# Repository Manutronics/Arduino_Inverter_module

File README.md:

# Arduino_Inverter_module
This repository made for inveter power module with serial interface which is be easily controlled by Arduino module such as pro mini or ESP8266
There is many modules in market that could help to perform smart IOT home project but unfortunately  there is rare product that  can use to control AC motor devices which is find in many home devices or appliance 
I gather all opensource information that I could  find yet  from design article to schematic file  and this is  really helpful to find proper approach to Arduino inverter module   
Fortunately there is very good IBGT power IC module with its BLDC driver from well known companies such as Infineon and Fairchild which is currently use in many  ready-to-use invertor product , following is couple of ICs  mostly find in midsize HVAC invertor boards
Fairchild  FSBB20CH60F  Motion SPM® 3 Series with FCM8201 3-Phase Sinusoidal Brushless DC Motor Controller  
Infineon  IRAMS06UP60A   with MC3PHAC Monolithic Intelligent Motor Controller

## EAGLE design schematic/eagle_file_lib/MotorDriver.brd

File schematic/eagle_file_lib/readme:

this are sketches from some open source comminunity and thanks to akpc806a for his sketch
https://github.com/akpc806a/Fairchild_MotionSPM_Powerstage

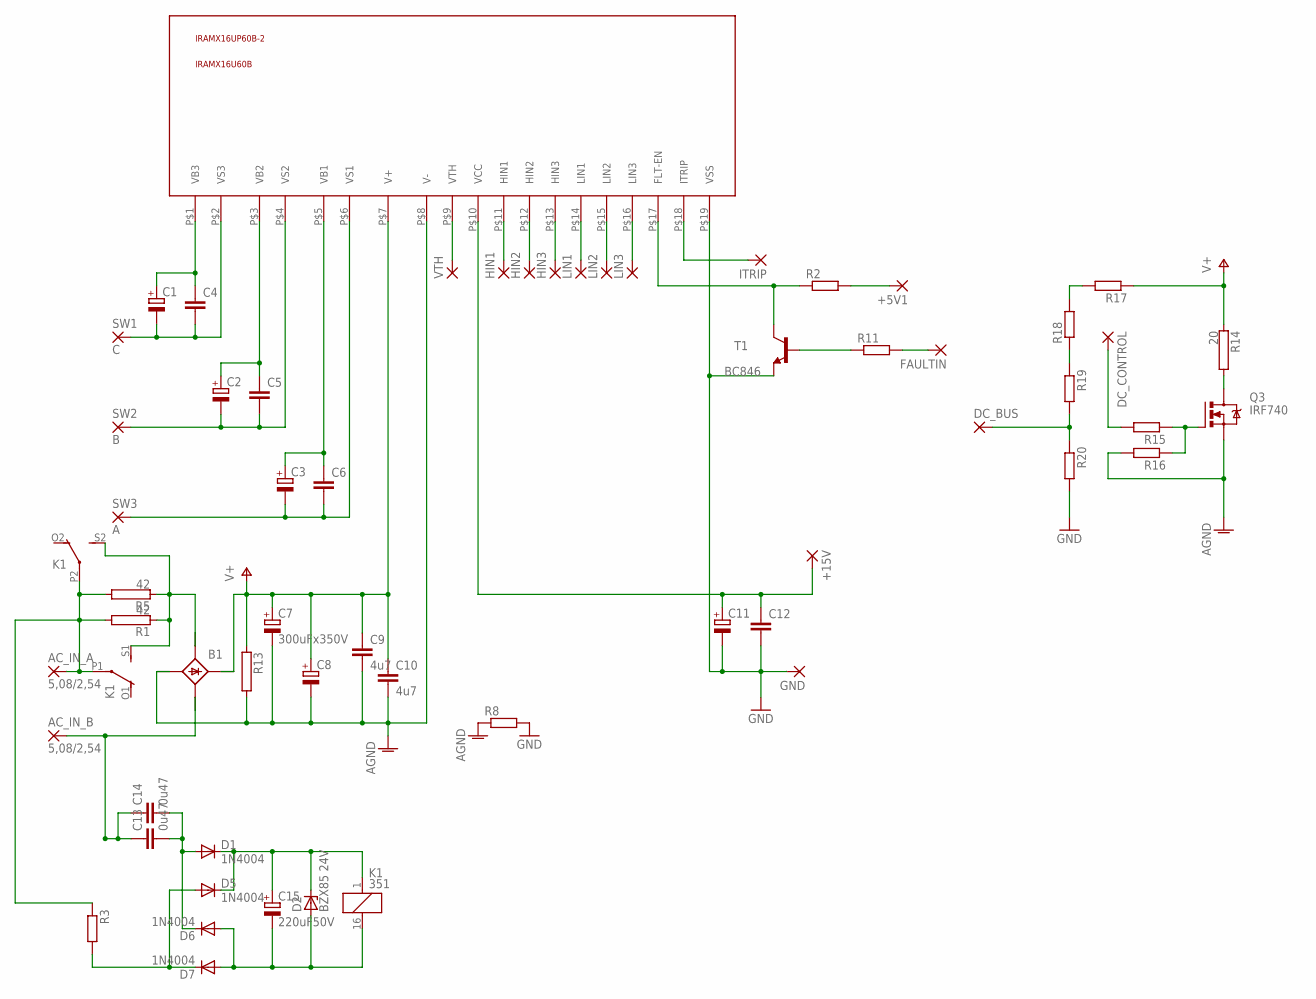
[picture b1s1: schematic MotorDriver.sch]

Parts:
+5V1, +15V: 3,81/1,3
AC_IN_A: 5,08/2,54
AC_IN_B: 5,08/2,54
B1: B25A-
C1, C2, C3, C11: CPOL-EUE2,5-6E; E2,5-6E
C4, C5, C6, C12: C-EUC1206; C1206
C7: 300uFx350V; EB35D
C8: CPOL-EUE10-35; EB35D
C9, C10: 4u7; C225-074X268
C13, C14: 0u47; C102-064X133
C15: 220uF50V; E3,5-10
D1, D5, D6, D7: 1N4004; DO41-10
D2: BZX85 24V; DO41Z10
DC_BUS: 3,81/1,3
DC_CONTROL: 3,81/1,3
FAULTIN: 3,81/1,3
GND: 3,81/1,3
HIN1, HIN2, HIN3: 2,54/0,8
IC1: IRAMX16UP60B-2; SIP2
ITRIP: 2,54/0,8
K1: 351
LIN1, LIN2, LIN3: 2,54/0,8
Q3: IRF740; TO220BV
R1, R5: 42; AC05
R2, R3, R8, R11, R15, R16, R17, R18, R19, R20: R-EU_0204/7; 0204/7
R13: RAC04; AC04
R14: 20; AC05
SW1: C; 5,08/2,54
SW2: B; 5,08/2,54
SW3: A; 5,08/2,54
T1: BC846; SOT23
VTH: 2,54/0,8

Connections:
AGND: B1.-, B1.-1 (-), C7.-, C8.-, C9.2, C10.2, IC1.P$8 (V-), Q3.S, R8.1, R13.2, R16.2
GND: C11.-, C12.2, GND.1, IC1.P$19 (VSS), R8.2, R20.2, T1.2 (E)
unnamed: C1.+, C4.1, IC1.P$1 (VB3)
unnamed: C2.+, C5.1, IC1.P$3 (VB2)
unnamed: C3.+, C6.1, IC1.P$5 (VB1)
unnamed: C1.-, C4.2, IC1.P$2 (VS3), SW1.P$1
unnamed: C2.-, C5.2, IC1.P$4 (VS2), SW2.P$1
unnamed: C3.-, C6.2, IC1.P$6 (VS1), SW3.P$1
unnamed: IC1.P$9 (VTH), VTH.1
unnamed: AC_IN_A.P$1, K1.P1, K1.P2, R1.2, R3.1, R5.2
unnamed: Q3.D, R14.2
unnamed: IC1.P$18 (ITRIP), ITRIP.1
unnamed: R11.1, T1.1 (B)
unnamed: IC1.P$16 (LIN3), LIN3.1
unnamed: FAULTIN.1, R11.2
unnamed: IC1.P$17 (FLT-EN), R2.1, T1.3 (C)
unnamed: IC1.P$15 (LIN2), LIN2.1
unnamed: IC1.P$14 (LIN1), LIN1.1
unnamed: HIN3.1, IC1.P$13 (HIN3)
unnamed: HIN2.1, IC1.P$12 (HIN2)
unnamed: HIN1.1, IC1.P$11 (HIN1)
unnamed: C13.2, C14.2, D1.A, D6.C
unnamed: D5.A, D7.C, R3.2
unnamed: DC_CONTROL.1, R15.2
unnamed: Q3.G, R15.1, R16.1
unnamed: B1.AC1, B1.AC1- (AC1), K1.S1 (S), K1.S2 (S), R1.1, R5.1
unnamed: DC_BUS.1, R19.2, R20.1
unnamed: +15V.1, C11.+, C12.1, IC1.P$10 (VCC)
unnamed: C15.-, D2.A, D6.A, D7.A, K1.16 (2)
unnamed: C15.+, D1.C, D2.C, D5.C, K1.1
unnamed: +5V1.1, R2.2
unnamed: R17.2, R18.2
unnamed: AC_IN_B.P$1, B1.AC2, B1.AC2- (AC2), C13.1, C14.1
unnamed: R18.1, R19.1
V+: B1.+, B1.+1 (+), C7.+, C8.+, C9.1, C10.1, IC1.P$7 (V+), R13.1, R14.1, R17.1

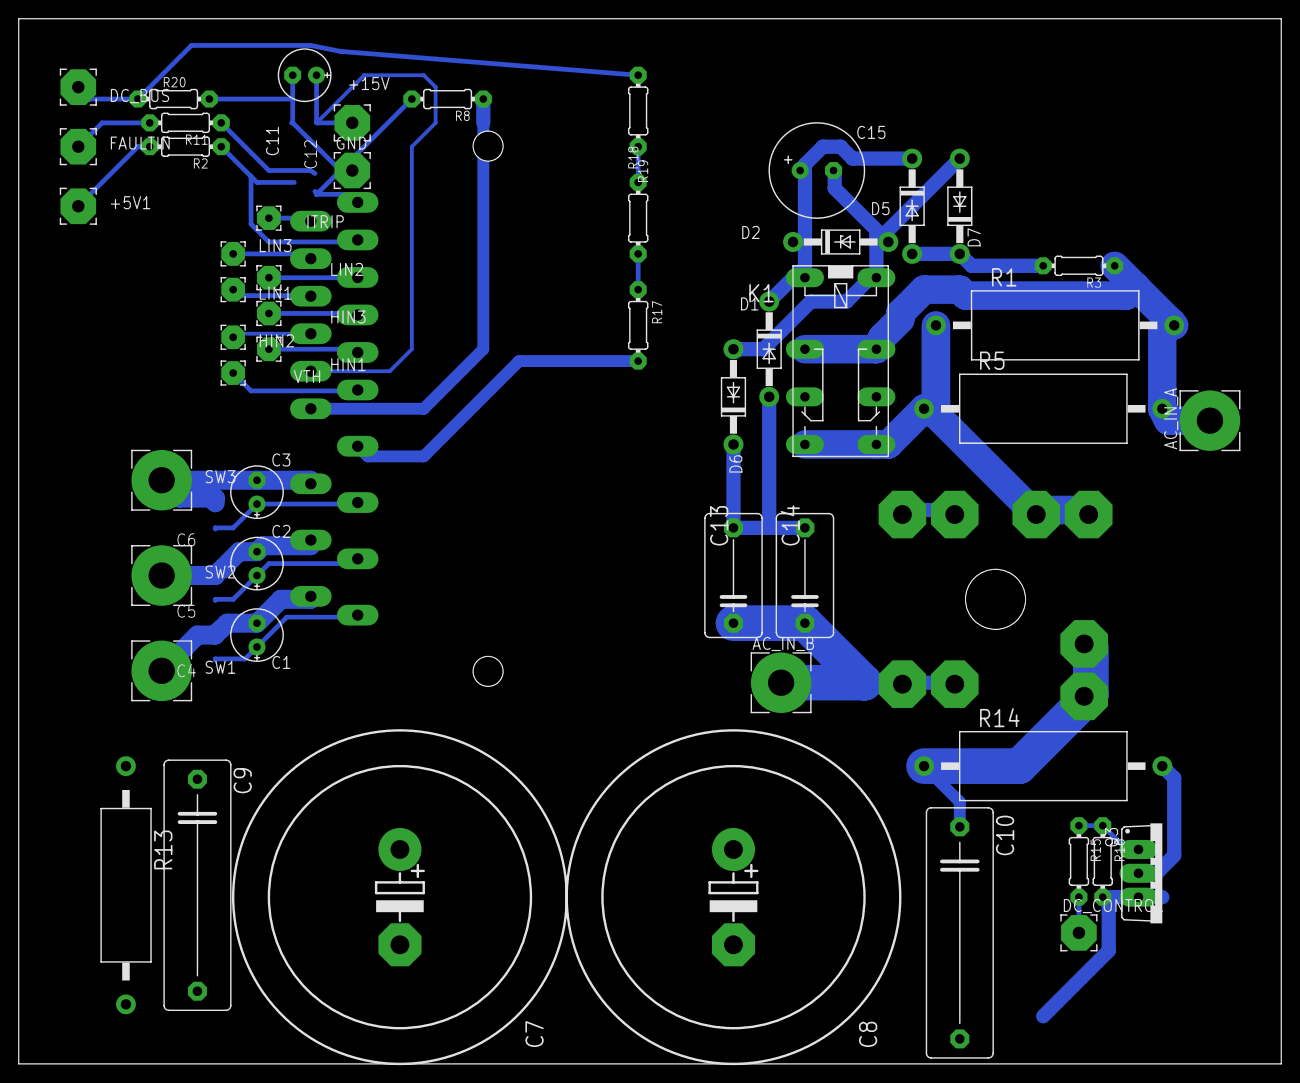
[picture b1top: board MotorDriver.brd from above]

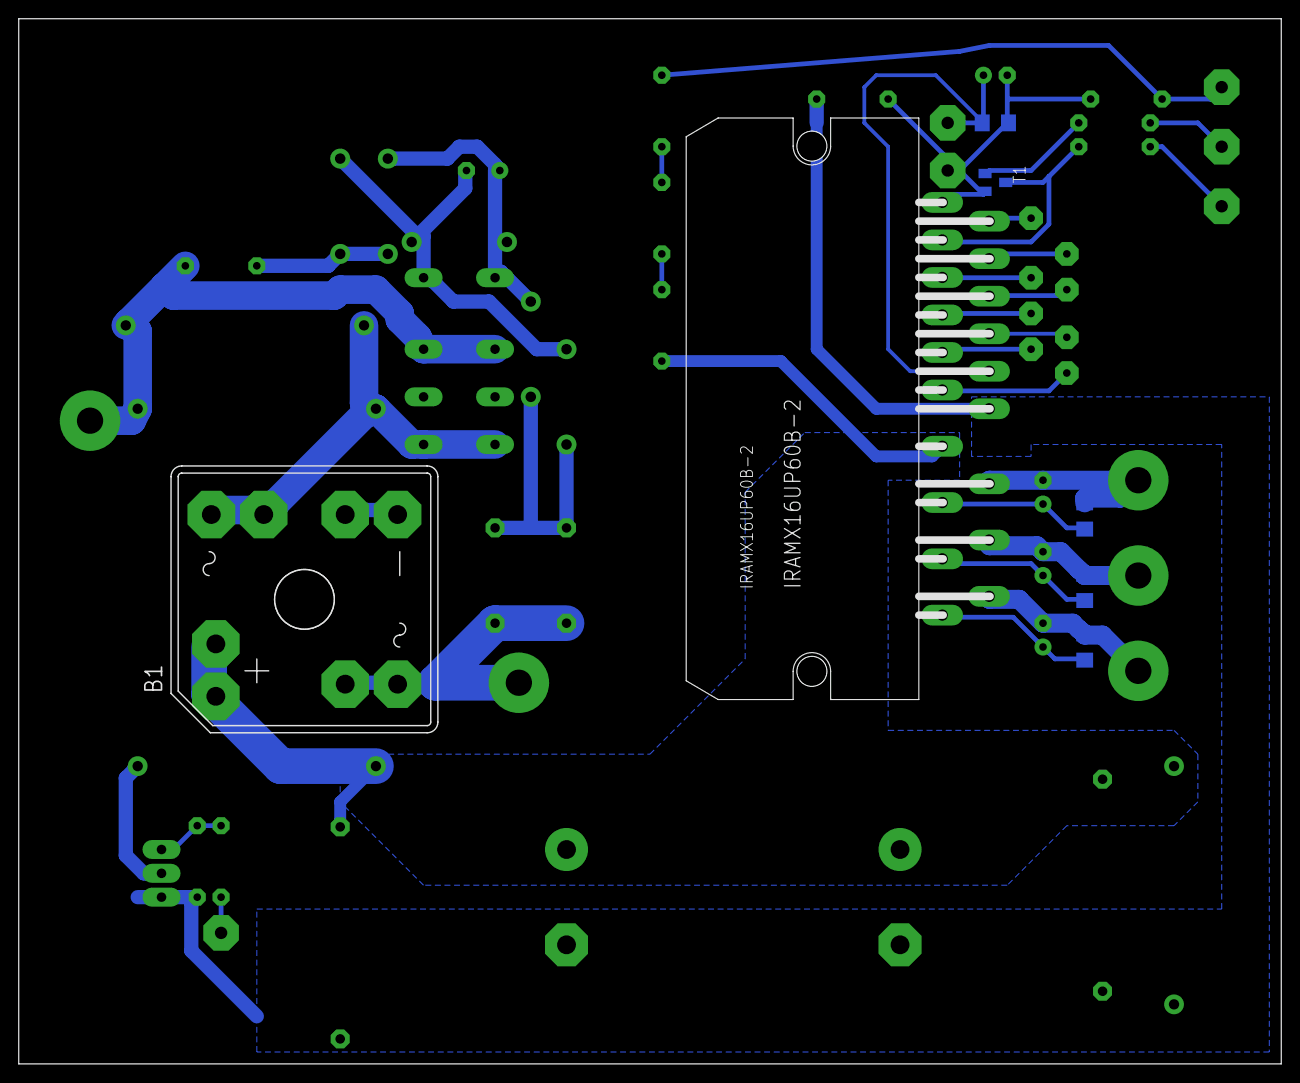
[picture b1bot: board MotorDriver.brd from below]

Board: 2 copper layers, 134.6 x 111.4 mm, 58 parts (7 on the bottom side), 35 nets.

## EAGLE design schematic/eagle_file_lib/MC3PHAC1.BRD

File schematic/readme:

this is repository  for eagle file of inveter boards

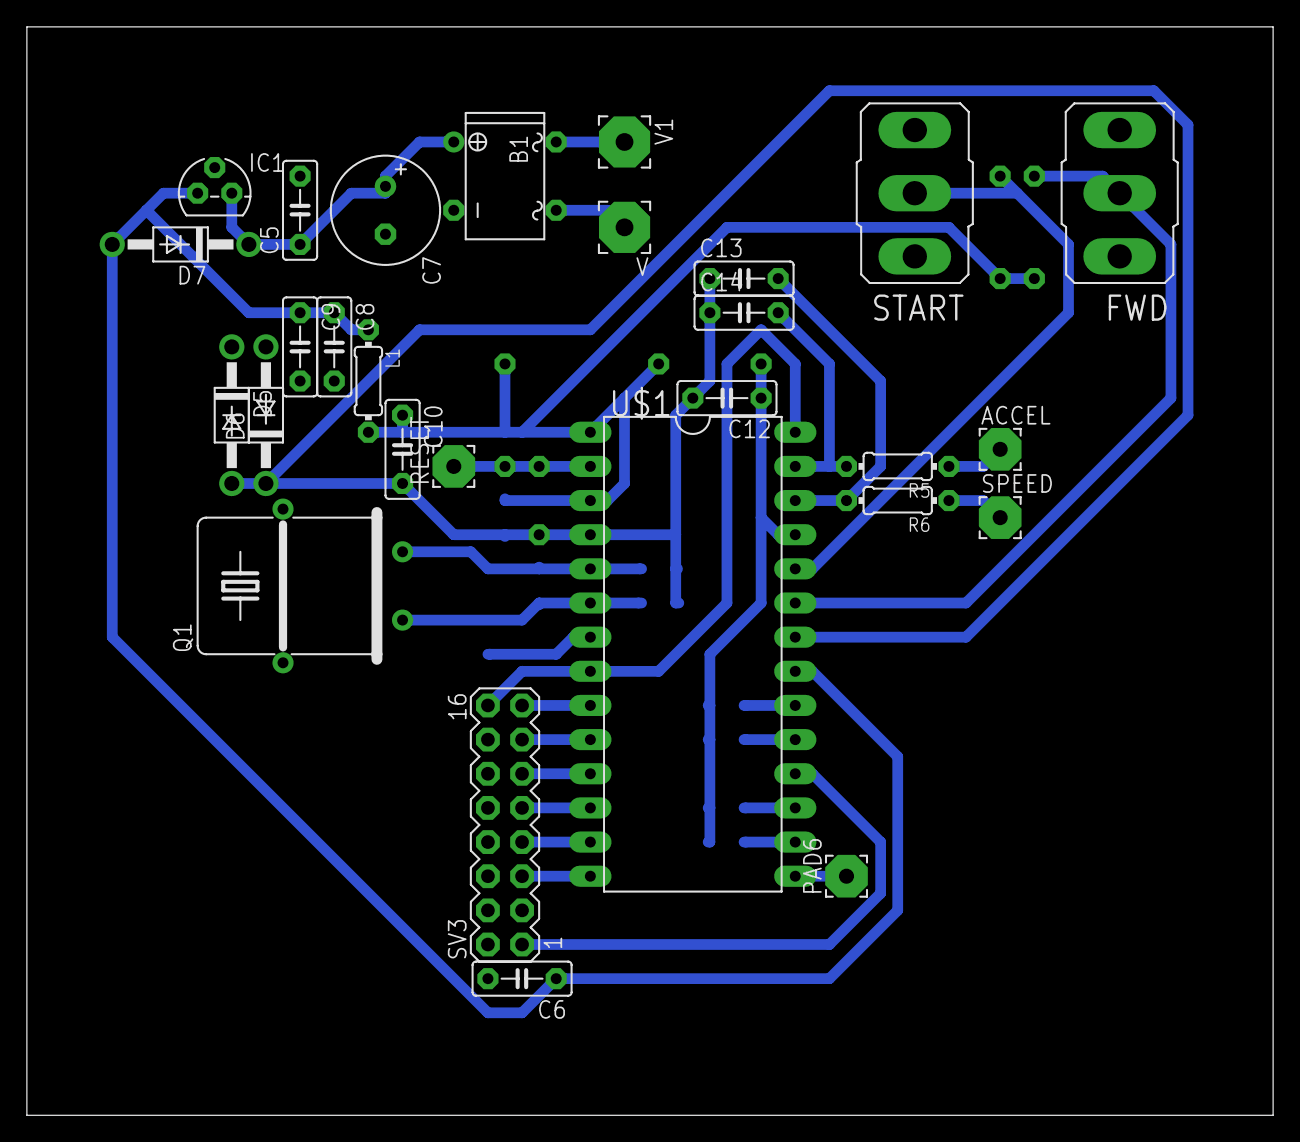
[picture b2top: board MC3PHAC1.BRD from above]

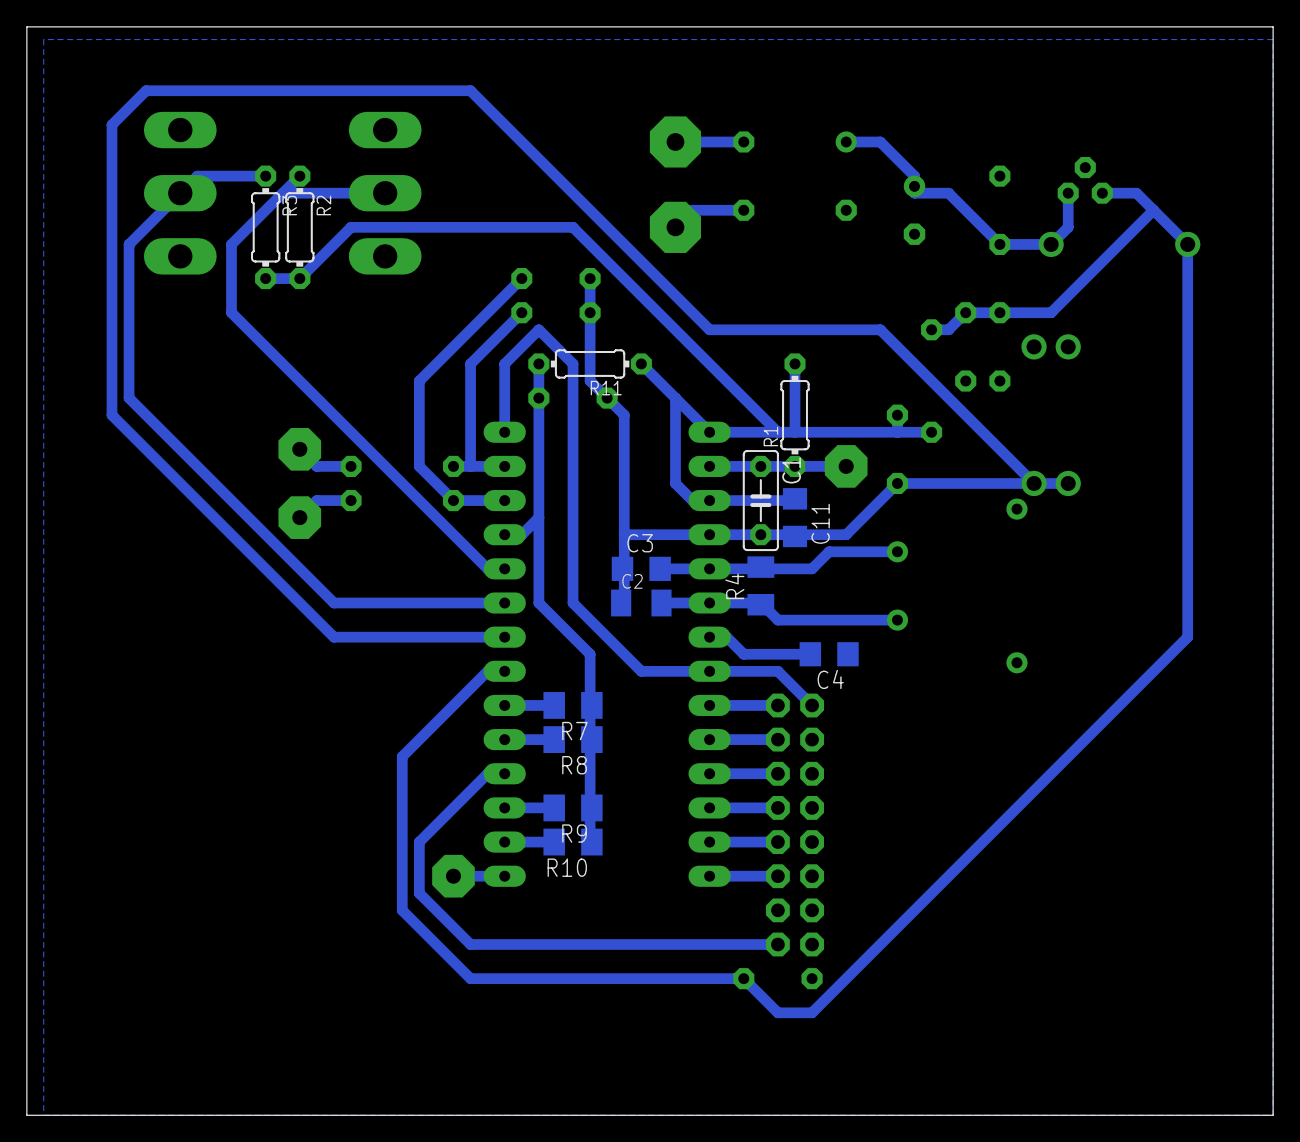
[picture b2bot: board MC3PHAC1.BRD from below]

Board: 2 copper layers, 92.7 x 81.0 mm, 42 parts (14 on the bottom side), 31 nets.

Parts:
ACCEL: 3,17/1,1
B1: B-DIL
C1, C12: 100n; C050-025X075
C2: 22p; C1206K
C3: 22p; C1206
C4: 100n; C1206
C5, C6, C8, C9, C10, C13, C14: C050-025X075
C7: E3,5-8
C11: C1206
D5, D6, D7: 1N4004; DO41-10
FWD: M9040P
IC1: 7805L; TO92
L1: 0204/7
PAD6: 3,17/1,1
Q1: HC18U-H
R1, R2, R3, R11: 10k; 0204/7
R4: 10M; M1206
R5, R6: 4k7; 0204/7
R7, R8, R9, R10: 10k; M1206
RESET: 3,17/1,1
SPEED: 3,17/1,1
START: M9040P
SV3: MA08-2
U$1: MC3PHAC; DIP-28
V, V1: V; 3,81/1,3

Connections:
+3V3: C6.1, C8.1, C9.1, D7.A, IC1.1, L1.1, U$1.21
+5VANALOG: C10.1, C11.1, L1.2, R1.2, R2.2, R3.2, R11.1, U$1.1, U$1.3
GND: B1.-, C4.1, C5.2, C6.2, C7.-, C8.2, C9.2, D5.C, D6.A, FWD.3, IC1.2, START.3, SV3.2, SV3.4, SV3.6, SV3.8, SV3.10, SV3.12, SV3.14
GNDA: C1.2, C2.1, C3.1, C10.2, C11.2, C12.2, C13.1, C14.1, D5.A, D6.C, U$1.4, U$1.22
unnamed: C1.1, R1.1, RESET.1, U$1.2
unnamed: R2.1, START.2, U$1.24
unnamed: FWD.2, R3.1, U$1.23
unnamed: C3.2, Q1.2, R4.2, U$1.5
unnamed: C2.2, Q1.1, R4.1, U$1.6
unnamed: C14.2, R5.2, U$1.27
unnamed: C4.2, U$1.7
unnamed: SV3.16, U$1.8, U$1.28
unnamed: C13.2, R6.2, U$1.26
unnamed: ACCEL.1, R5.1
unnamed: R6.1, SPEED.1
unnamed: SV3.1, U$1.18
unnamed: PAD6.1, U$1.15
unnamed: C12.1, R7.1, R8.1, R9.1, R10.1, R11.2, U$1.25
unnamed: R7.2, U$1.20
unnamed: R8.2, U$1.19
unnamed: R9.2, U$1.17
unnamed: R10.2, U$1.16
unnamed: SV3.5, U$1.14
unnamed: SV3.7, U$1.13
unnamed: SV3.9, U$1.12
unnamed: SV3.11, U$1.11
unnamed: SV3.13, U$1.10
unnamed: SV3.15, U$1.9
unnamed: B1.AC2, V1.1
unnamed: B1.+, C5.1, C7.+, D7.C, IC1.3
unnamed: B1.AC1, V.1

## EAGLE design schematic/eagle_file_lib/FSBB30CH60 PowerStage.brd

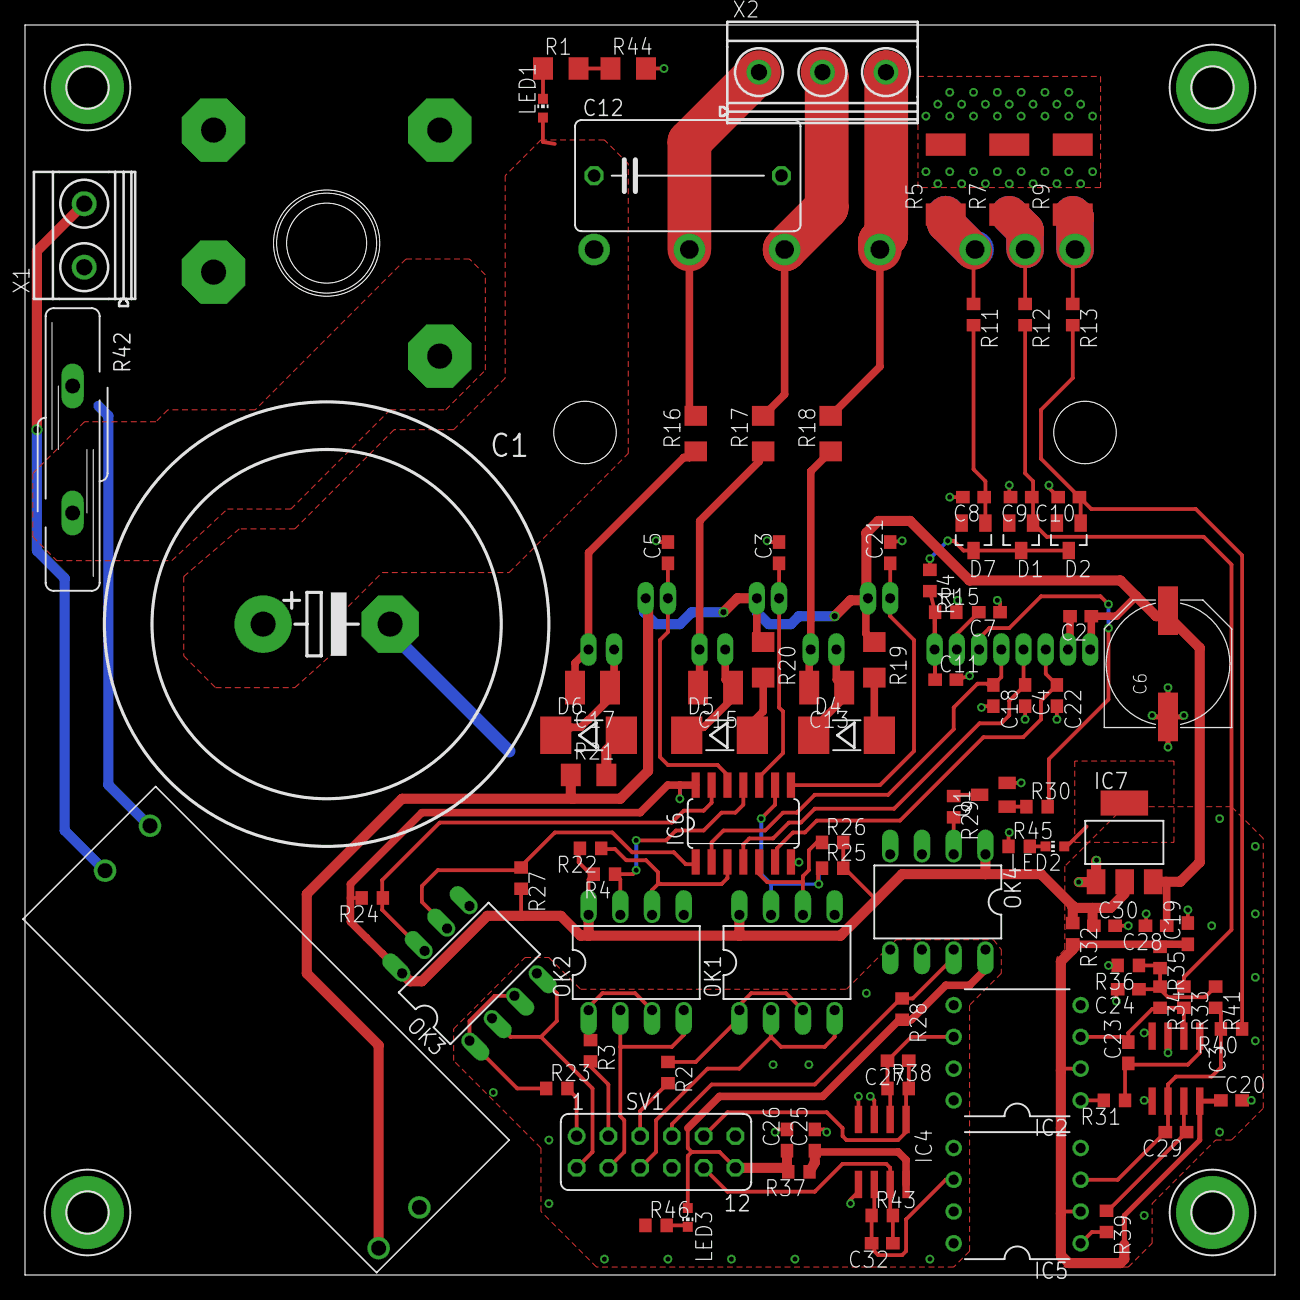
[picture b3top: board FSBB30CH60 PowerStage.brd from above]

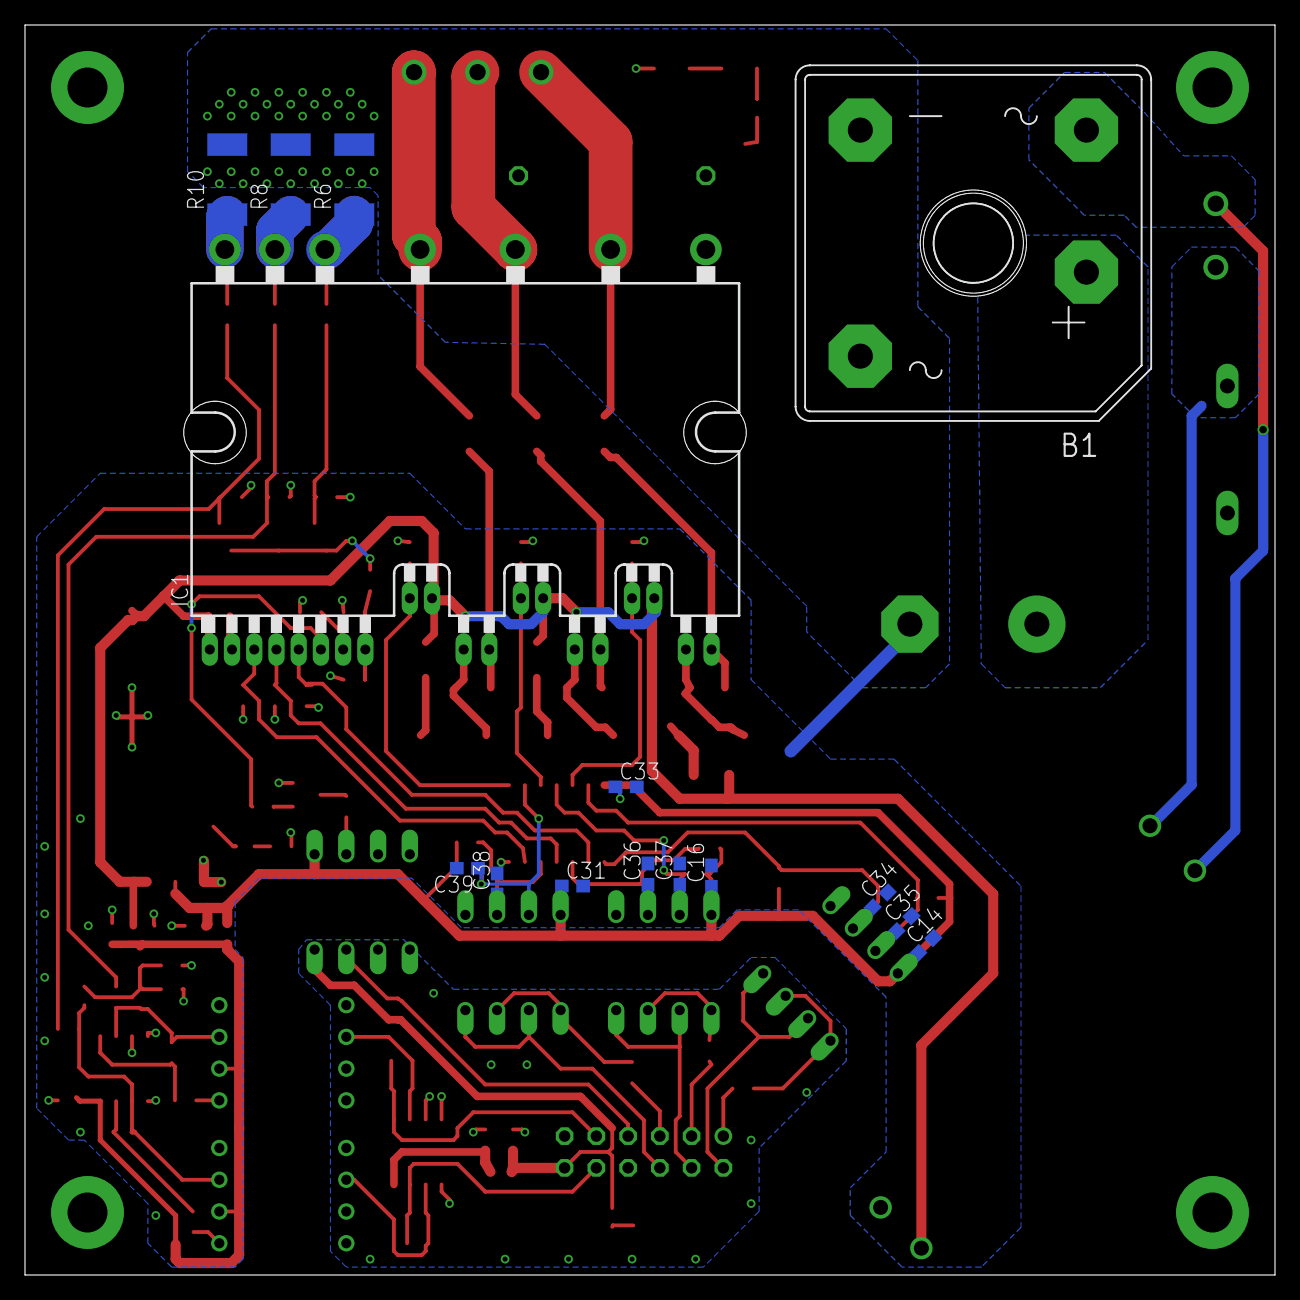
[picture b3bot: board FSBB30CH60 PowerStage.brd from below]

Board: 2 copper layers, 100.0 x 100.0 mm, 115 parts (15 on the bottom side), 73 nets.

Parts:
B1: GBPC3510W; GBPC-W
C1: 470 uF 450 V; EB35D
C2, C14, C16, C19, C20, C24, C25, C26, C31, C33: 0.1 uF; C0603
C3, C4, C5, C11, C18, C21, C22, C34, C35, C36, C37, C38, C39: 10 nF; C0603
C6: 220 uF 25 V; PANASONIC_G
C7: 33 nF; C0603
C8, C9, C10, C23, C27, C29, C32: 1 nF; C0603
C12: 0.22 uF 630 V; C150-091X182
C13: 10 uF x 50 V; C1210
C15, C17: 10 uF 50 V; C1210
C28, C30: 1 uF; C0603
D1, D2, D7: BAT54; SOT23
D4, D5, D6: SM4937; MELF-MLL41
H1, H2, H3, H4: MOUNT-PAD-ROUND3.2; 3,2-PAD
IC1: FSBB30CH60
IC2, IC5: HCNR200; DIL08-400
IC3: SO08
IC4: LM358D; SO08
IC6: 74HCT04D; SO14
IC7: REG1117; SOT223
LED1, LED2, LED3: CHIP-LED0603
OK1, OK2, OK3, OK4: HCPL2530; DIL08
Q1: BC817-16SMD; SOT23-BEC
R1, R44: 68 k; R1206
R2, R3, R23, R45, R46: 220; R0603
R4, R22, R24, R25, R26, R27, R28, R30: 2 k; R0603
R5, R6, R7, R8, R9, R10: 0.1; R2512
R11, R12, R13, R29: 330; R0603
R14, R36: 1 k; R0603
R15: 47 k; R0603
R16, R17, R18: 5.6; R1206
R19, R20, R21: 20; R1206
R31, R39: 200; R0603
R32, R37: 10; R0603
R33, R34, R40, R41: 33 k; R0603
R35: 6.8 k; R0603
R38, R43: 51 k; R0603
R42: NTC-10D25; S20K40
SV1: FE06-2
U$1: KUUKO_090873
X1: MKDSN1,5/2-5,08
X2: MKDSN1,5/3-5,08

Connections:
+5V: C14.1, C16.1, C30.1, C31.1, C33.1, IC6.14, IC7.2, IC7.4, LED2.A, OK1.8, OK2.8, OK3.8, OK4.1, R4.2, R22.2, R24.2, R25.2, R26.2, R27.2, R32.1
+15V: C2.1, C6.+, C28.1, IC1.1, IC1.10, IC1.14, IC1.18, IC7.3, R19.1, R20.1, R21.1, U$1.P
+300V: B1.+1, C1.+, C12.1, IC1.27, LED1.A
FAULT: OK4.7, R28.1, SV1.7
GND: B1.-1, C1.-, C2.2, C3.2, C4.2, C5.2, C6.-, C7.1, C8.2, C9.2, C10.2, C11.2, C12.2, C14.2, C16.2, C18.2, C19.2, C20.2, C21.2, C22.2, C24.2, C28.2, C30.2, C31.2, C33.2, C34.2, C35.2, C36.2, C37.2, C38.2, C39.2, IC1.2, IC2.4, IC3.3, IC3.4, IC3.5, IC5.4, IC6.7, IC7.1, OK1.5, OK2.5, OK3.5, Q1.E, R5.2, R6.2, R7.2, R8.2, R9.2, R10.2, R15.2, R36.2, R44.2, R45.1, U$1.M
GNDIO: C25.2, C26.2, IC2.5, IC4.3, IC4.4, IC4.5, IC5.5, OK4.5, R46.1, SV1.11
INUH: C21.1, IC1.9, IC6.8
INUL: C22.1, IC1.3, IC6.6
INVH: C3.1, IC1.13, IC6.10
INVL: C4.1, IC1.4, IC6.4
INWH: C5.1, IC1.17, IC6.12
INWL: C18.1, IC1.5, IC6.2
I_U: C10.1, D2.1, R13.2, R40.1
I_U_OUT: C32.1, IC4.7, R43.2, SV1.10
I_V: C9.1, D1.1, R12.2, R33.1
I_V_OUT: C27.1, IC4.1, R38.2, SV1.9
I_W: C8.1, D7.1, R11.2
unnamed: IC1.23, R5.1, R6.1, R11.1
unnamed: OK1.1, OK1.3, R2.1
unnamed: B1.AC1-, R42.2
unnamed: B1.AC2-, U$1.AC1, X1.2
unnamed: IC1.26, R16.2, X2.1
unnamed: IC1.25, R17.2, X2.2
unnamed: IC1.24, R18.2, X2.3
unnamed: IC5.1, R39.2
unnamed: C25.1, IC4.8, R37.1
unnamed: IC1.22, R7.1, R8.1, R12.1
unnamed: IC1.21, R9.1, R10.1, R13.1
unnamed: C7.2, IC1.7
unnamed: D1.3, D2.3, D7.3, R14.1
unnamed: C11.1, IC1.8, R14.2, R15.1
unnamed: C13.1, D4.C, IC1.11
unnamed: C13.2, IC1.12, R18.1
unnamed: D4.A, R19.2
unnamed: C15.1, D5.C, IC1.15
unnamed: C15.2, IC1.16, R17.1
unnamed: D5.A, R20.2
unnamed: C17.1, D6.C, IC1.19
unnamed: C17.2, IC1.20, R16.1
unnamed: D6.A, R21.2
unnamed: OK4.2, R29.2
unnamed: Q1.C, R29.1
unnamed: Q1.B, R30.1
unnamed: C23.2, IC2.3, IC3.2, R33.2, R34.2
unnamed: OK2.1, OK2.3, R3.1
unnamed: C27.2, IC2.6, IC4.2, R38.1
unnamed: OK3.1, OK3.3, R23.1
unnamed: C39.1, IC6.9, OK1.7, R25.1
unnamed: C29.2, IC3.6, IC5.3, R40.2, R41.2
unnamed: C29.1, IC3.7, R39.1
unnamed: C23.1, IC3.1, R31.1
unnamed: C32.2, IC4.6, IC5.6, R43.1
unnamed: IC2.1, R31.2
unnamed: C38.1, IC6.5, OK1.6, R26.1
unnamed: C37.1, IC6.11, OK2.7, R4.1
unnamed: C36.1, IC6.3, OK2.6, R22.1
unnamed: C35.1, IC6.13, OK3.7, R24.1
unnamed: C34.1, IC6.1, OK3.6, R27.1
unnamed: LED1.C, R1.1
unnamed: R1.2, R44.1
unnamed: LED2.C, R45.2
unnamed: LED3.C, R46.2
unnamed: R42.1, U$1.AC2, X1.1
PWM_U_H: R2.2, SV1.5
PWM_U_L: OK1.2, OK1.4, SV1.6
PWM_V_H: R3.2, SV1.3
PWM_V_L: OK2.2, OK2.4, SV1.4
PWM_W_H: R23.2, SV1.1
PWM_W_L: OK3.2, OK3.4, SV1.2
U_REF: C24.1, R34.1, R35.2, R36.1, R41.1
VCCA: C19.1, C20.1, IC2.2, IC3.8, IC5.2, R32.2, R35.1
VCCIO: C26.1, LED3.A, OK4.8, R28.2, R37.2, SV1.12
VFO: IC1.6, R30.2

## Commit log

2016-08-05 Add files via upload
    images
